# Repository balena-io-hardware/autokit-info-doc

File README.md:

The AutoKit (Automation Kit) is a platform that enables hands-free, automated interaction with electronic hardware. It's a package of hardware and software with a simple interface.

## Architecture

The goal is to have a "standard" package that can be used in a range of automation use cases, such as automated testing. There are many ways one could create a device that fits with their specific scenario - however, AutoKit should provide a "one-box" solution that can be shipped and deployed, with confidence that it will provide some clearly defined capabilities, with a clearly defined interface. Those without the hardware, software knowledge or time to develop their own automation tool can simply use this one.

Another goal is to manage AutoKit as a platform - users should be providing feedback, and community contribution should be enabled and encouraged. This is the only way to scale the platform and let it become the "general" solution for automated interaction with hardware.

Based on these goals, the architecture should keep the following mantras in mind:

- Use hardware that is openly available or open source
- Have a single common, widely used interface
- Features should be decoupled from each other where possible
- Standardize hardware - but at the same time, make it easily replaced or substituted

### Hardware

AutoKit is designed around a USB hub and a collection of USB devices. The hub is connected to the a computer that will run the AutoKit software suite, while the USB devices connect to the hub and implement the "actions" that one would want to automate on the DUT.

The suite of hardware currently envisioned:

- USB hub (any)
- [SD card multiplexer](https://github.com/balena-io-hardware/autokit-sd-mux) 
- [Mains relay controller](https://github.com/balena-io-hardware/autokit-relay)
- [USB HDMI capture device](https://www.amazon.co.uk/dp/B093D6824V/ref=sspa_dk_detail_3?psc=1&pd_rd_i=B093D6824V&pd_rd_w=MhHqo&content-id=amzn1.sym.1d17a7d9-68f2-46c6-a55b-f888c57f8c2e&pf_rd_p=1d17a7d9-68f2-46c6-a55b-f888c57f8c2e&pf_rd_r=3KSV1G8M649W5X9N7X52&pd_rd_wg=pxzYg&pd_rd_r=4254f3c1-ea0e-4e47-aebf-22eccee1f69d&s=electronics&sp_csd=d2lkZ2V0TmFtZT1zcF9kZXRhaWw&spLa=ZW5jcnlwdGVkUXVhbGlmaWVyPUEySEsyQUxEVUVWR1Q2JmVuY3J5cHRlZElkPUEwNTgyNzc4MkVaTUZITDBEVkdBSSZlbmNyeXB0ZWRBZElkPUEwMzA5NzQ1MlZYMkVCWEM3RTRXVCZ3aWRnZXROYW1lPXNwX2RldGFpbCZhY3Rpb249Y2xpY2tSZWRpcmVjdCZkb05vdExvZ0NsaWNrPXRydWU=)
- [USB to Ethernet adapter](https://www.amazon.co.uk/AmazonBasics-1000-Gigabit-Ethernet-Adapter/dp/B00M77HMU0)
- [USB microphone adapter](https://www.amazon.co.uk/gp/product/B00IRVQ0F8/ref=ppx_yo_dt_b_asin_title_o06_s00?ie=UTF8&psc=1)
- [USB UART adapter](https://ftdichip.com/products/ttl-232r-3v3/)

#### Why USB?

USB is a standard interface, and there are many sensors and actuators that use USB. Using USB lets any device act as the host for the automation kit - a laptop, a Raspberry Pi, a NUC, an etcherPro...

There may be devices that are "better" for a specific use case than a USB equivalent - for example, perhaps a CSI camera provides higher bandwidth than a USB one. However, not all host devices may have a CSI port. Making exceptions for interfaces like this is a slippery slope, and the danger is that we're left with a big collection of different interfaces, instead of one universal one.

### Enclosure and assembly

[Assembly guide and BoM](https://github.com/balena-io-hardware/autokit-assembly)

### Software

[AutoKit software interface](https://github.com/balena-io-hardware/autokit-sw)

## Capabilities

These are the first proposed features for AutoKit. These are based on the project's initial purpose, which was a tool to automate the provisioning and testing of embedded Linux SBCs.

- Multiplexing an SD card between the automation kit host, and the device under test (DUT)
- Controlling the power of a DUT
- Providing an Ethernet connection to the DUT
- Providing a Wi-Fi connection to the DUT
- Capturing HDMI output from the DUT
- Capturing sound output from the DUT
- Capturing serial output from the DUT

## Interface

- USB
- Host capable of running Docker containers

## Contributing

1. Identify a feature or capability that you desire- e.g voltmeter
2. Find a USB device that has that functionality - or design it!
3. Add that device to the [supported devices list](https://github.com/balena-io-hardware/autokit-assembly)
4. Add the software interface following the instructions [here](https://github.com/balena-io-hardware/autokit-sw)
5. Update the capabilities list above

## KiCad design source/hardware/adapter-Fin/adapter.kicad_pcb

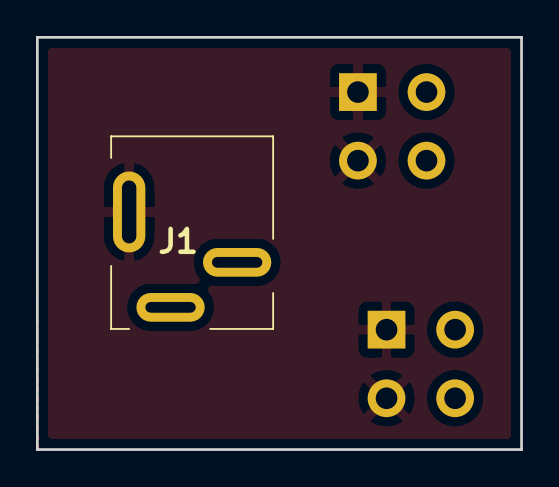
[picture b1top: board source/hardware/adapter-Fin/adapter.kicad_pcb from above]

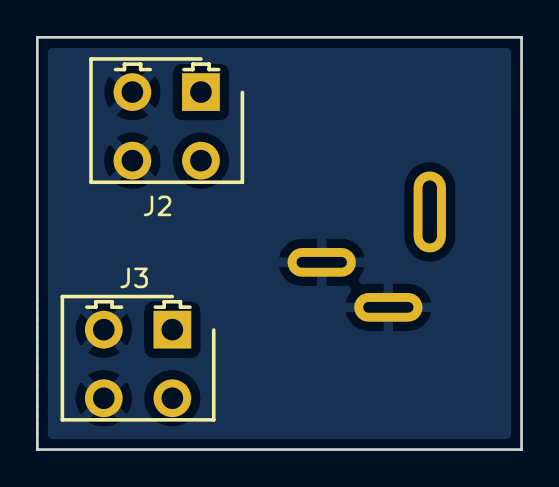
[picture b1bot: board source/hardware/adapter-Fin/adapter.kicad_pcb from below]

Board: 2 copper layers, 26.9 x 22.9 mm, 3 parts (2 on the bottom side), 2 nets, no tracks yet.

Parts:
J1: Barrel_Jack_Switch; Wurth_694108402002
J2, J3: Phoenix_IMC_1862577; PhoenixContact_IMCV_1777710

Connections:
GND: J1.2, J1.3, J2.3, J2.4, J3.3, J3.4
VCC: J1.1, J2.1, J2.2, J3.1, J3.2

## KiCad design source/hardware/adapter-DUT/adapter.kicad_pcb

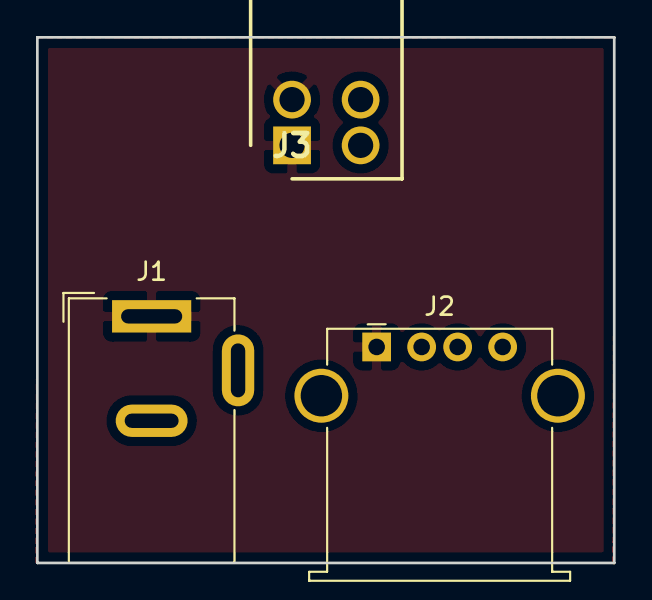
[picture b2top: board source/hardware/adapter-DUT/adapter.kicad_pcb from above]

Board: 2 copper layers, 32.0 x 29.2 mm, 3 parts (0 on the bottom side), 2 nets, no tracks yet.

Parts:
J1: Barrel_Jack_Switch; BarrelJack_Wuerth_6941xx301002
J2: USB_A; USB_A_Stewart_SS-52100-001_Horizontal
J3: Phoenix_IMC_1862577; PhoenixContact_IMC_1862577

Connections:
GND: J1.2, J1.3, J2.4, J2.5, J3.3, J3.4
VCC: J1.1, J2.1, J3.1, J3.2

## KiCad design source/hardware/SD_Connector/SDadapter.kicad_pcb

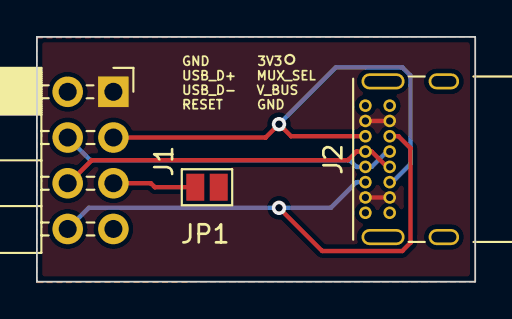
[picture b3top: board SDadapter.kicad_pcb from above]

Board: 2 copper layers, 24.3 x 13.6 mm, 3 parts (0 on the bottom side), 7 nets.

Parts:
J1: Conn_02x04_Odd_Even; PinSocket_2x04_P2.54mm_Horizontal
J2: USB_C_Receptacle_USB2.0; USB_C_Receptacle_GCT_USB4085
JP1: SolderJumper_2_Open; SolderJumper-2_P1.3mm_Open_Pad1.0x1.5mm

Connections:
/3V3: J1.1, J2.A4, J2.A9, J2.B4, J2.B9
/RESET_N: J1.8, J2.A5, J2.B5
/SD_MUX_SEL: J1.3, J2.A8, J2.B8
/USB_DN: J1.6, J2.A7, J2.B7
/USB_DP: J1.4, J2.A6, J2.B6
GND: J1.2, J1.7, J2.A1, J2.A12, J2.B1, J2.B12
unnamed: J1.5, JP1.2

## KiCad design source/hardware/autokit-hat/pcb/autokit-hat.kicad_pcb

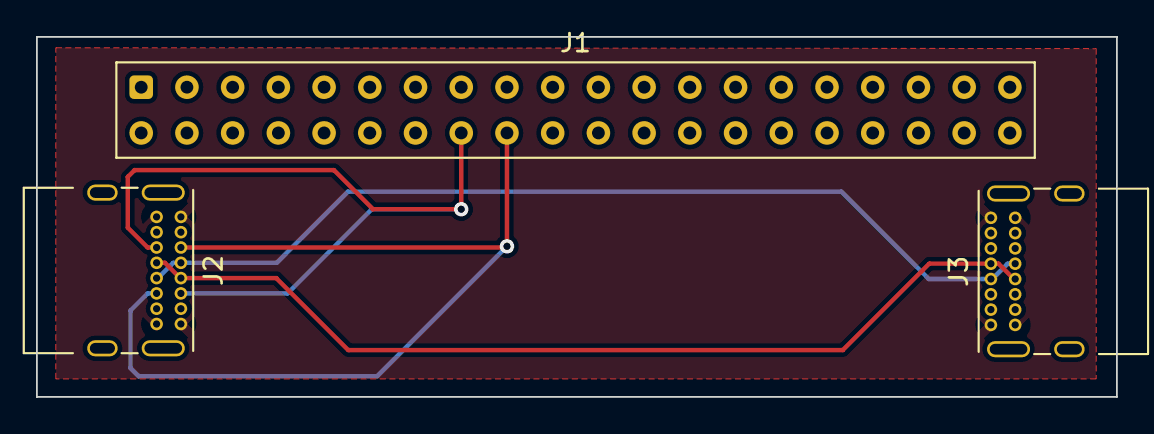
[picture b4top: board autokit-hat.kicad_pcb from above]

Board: 2 copper layers, 60.0 x 20.0 mm, 3 parts (0 on the bottom side), 6 nets.

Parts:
J1: Raspberry_Pi_2_3; Samtec_HLE-120-02-xx-DV-TE_2x20_P2.54mm_Horizontal
J2, J3: USB_C_Receptacle_USB2.0; USB_C_Receptacle_GCT_USB4085

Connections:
GND: J2.A1, J2.A12, J2.B1, J2.B12, J3.A1, J3.A12, J3.B1, J3.B12
SD_MUX_RST: J1.18, J2.A5, J2.B5
SD_MUX_SEL: J1.16, J2.A8, J2.B8
USB_DN: J2.A7, J2.B7, J3.A7, J3.B7
USB_PN: J2.A6, J2.B6, J3.A6, J3.B6
VCC: J2.A4, J2.A9, J2.B4, J2.B9, J3.A4, J3.A9, J3.B4, J3.B9

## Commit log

2022-02-14 add hardware files
    Change-type: major
2022-02-14 add software files
    Change-type: patch
2022-02-14 v1.0.0
2022-05-31 initially fill in readme
    Change-type: patch
2022-06-21 add testing file
    Change-type: patch
2022-06-21 v0.0.2
2022-06-23 add initial sw interface
    Change-type: patch
2022-06-23 v0.0.3
2022-08-22 fix typos and add sw and enclosure info
    Change-type: patch
2022-08-23 test PR - DO NOT MERGE
    Change-type: patch
2022-08-23 v0.0.4
2022-10-19 convert to flowzone
    Change-type: patch
2022-10-28 test commit
    Change-type: patch
2022-10-28 dont merge - test hardware-check
    Change-type: patch
2022-11-14 Add flowzone website build
    Change-type: patch
2022-11-21 Testing build with cloudflare
2022-11-21 v0.0.5
2023-01-31 Add logo and proofread README
    Change-type: patch
